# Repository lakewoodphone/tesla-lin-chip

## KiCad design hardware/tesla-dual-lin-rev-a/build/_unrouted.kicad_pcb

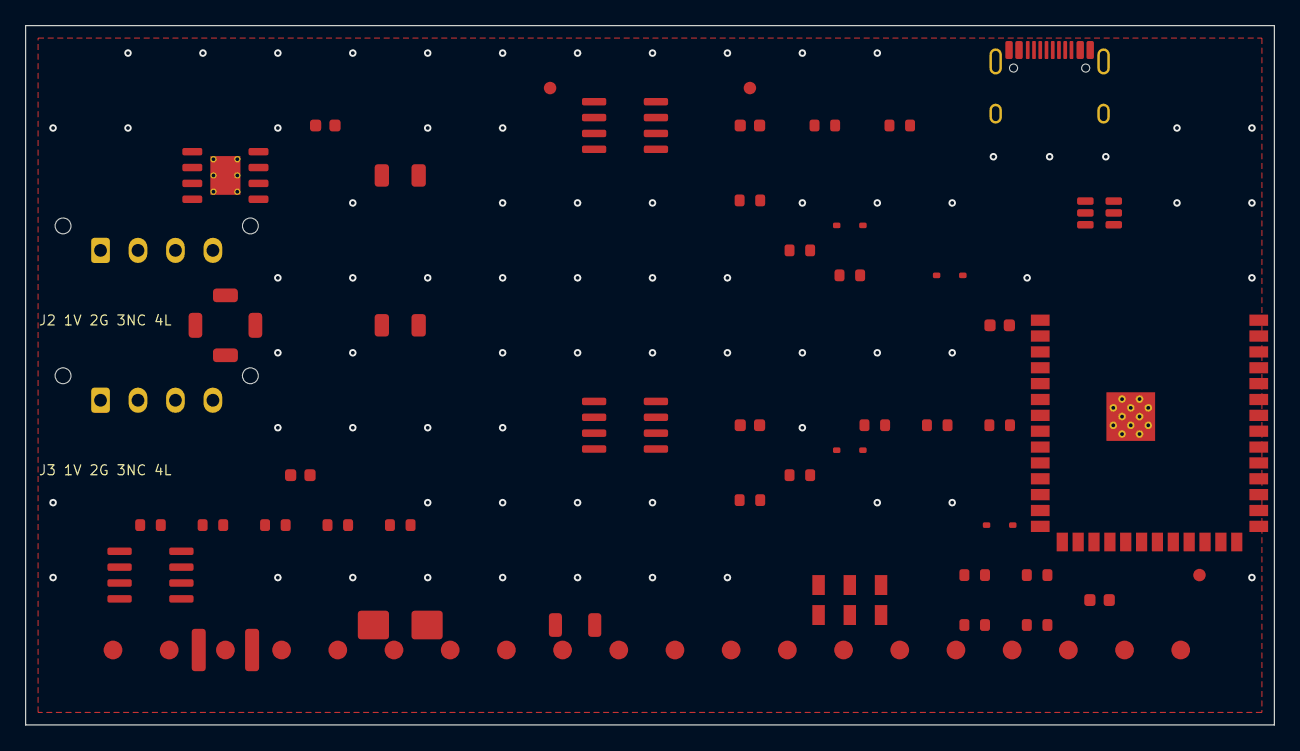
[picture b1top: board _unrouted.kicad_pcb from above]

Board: 4 copper layers, 100.0 x 56.0 mm, 72 parts (0 on the bottom side), 37 nets, no tracks yet.

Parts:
C_3V3: 22uF 10V; C_1206_3216Metric
C_BST1: 100nF; C_0603_1608Metric
C_EN1: 1uF 10V; C_0603_1608Metric
C_IN1: 10uF 50V; C_1206_3216Metric
C_U1_DEC1, C_U2_DEC1, C_U3_DEC1, C_U4_DEC1: 100nF; C_0603_1608Metric
D1: SMBJ24A; D_SMB
D2: LIN_A ESD; D_SOD-323
D3: LIN_B ESD; D_SOD-323
D4: USB ESD; SOT-23-6
D_LINA_MASTER1: DNP LIN master diode; D_SOD-323
D_LINB_MASTER1: DNP LIN master diode; D_SOD-323
F1: 1812 PPTC; Fuse_1812_4532Metric
FB1: 1206 ferrite; L_1206_3216Metric
FID1, FID2, FID3: FID; Fiducial_1mm_Mask2mm
J1: USB-C; USB_C_Receptacle_HRO_TYPE-C-31-M-12
J2: Molex Micro-Fit car service; Molex_Micro-Fit_3.0_43650-0415_1x04_P3.00mm_Vertical
J3: Molex Micro-Fit wheel service; Molex_Micro-Fit_3.0_43650-0415_1x04_P3.00mm_Vertical
L1: 10uH; L_Bourns_SRU5016_5.2x5.2mm
MH1, MH2, MH3, MH4: MH3.2; MountingHole_3.2mm_M3
Q1: AO4407A PFET; SOIC-8_3.9x4.9mm_P1.27mm
R_ARMSENSE_PD1: 0603; R_0603_1608Metric
R_BOOT1: 0603; R_0603_1608Metric
R_BUCK_EN1: 0603; R_0603_1608Metric
R_BUCK_RON1: 0603; R_0603_1608Metric
R_CC1, R_CC2: 0603; R_0603_1608Metric
R_EN1: 0603; R_0603_1608Metric
R_FB_BOT1: 0603; R_0603_1608Metric
R_FB_TOP1: 0603; R_0603_1608Metric
R_LINA_MASTER1: 0603; R_0603_1608Metric
R_LINA_SER1: 0603; R_0603_1608Metric
R_LINA_TXD_PU1: 0603; R_0603_1608Metric
R_LINB_MASTER1: 0603; R_0603_1608Metric
R_LINB_SER1: 0603; R_0603_1608Metric
R_LINB_TXD_PU1: 0603; R_0603_1608Metric
R_LINEN_PD1: 0603; R_0603_1608Metric
R_PGOOD_PU1: 0603; R_0603_1608Metric
R_WAKE_A1: 0603; R_0603_1608Metric
R_WAKE_B1: 0603; R_0603_1608Metric
SW1: DPDT ARM; SW_DPDT_CK_JS202011JCQN
TP1: GND; TestPoint_Pad_D1.5mm
TP2: 3V3; TestPoint_Pad_D1.5mm
TP3: VBAT; TestPoint_Pad_D1.5mm
TP4: USB-; TestPoint_Pad_D1.5mm
TP5: USB+; TestPoint_Pad_D1.5mm
TP6: UART_TX; TestPoint_Pad_D1.5mm
TP7: UART_RX; TestPoint_Pad_D1.5mm
TP8: EN; TestPoint_Pad_D1.5mm
TP9: BOOT; TestPoint_Pad_D1.5mm
TP10: LIN_A; TestPoint_Pad_D1.5mm
TP11: LIN_B; TestPoint_Pad_D1.5mm
TP12: LIN_A_TJA; TestPoint_Pad_D1.5mm
TP13: LIN_B_TJA; TestPoint_Pad_D1.5mm
TP14: LIN_EN; TestPoint_Pad_D1.5mm
TP15: LIN_EN_DRV; TestPoint_Pad_D1.5mm
TP16: ARM; TestPoint_Pad_D1.5mm
TP17: WAKE_A; TestPoint_Pad_D1.5mm
TP18: WAKE_B; TestPoint_Pad_D1.5mm
TP19: INH_A; TestPoint_Pad_D1.5mm
TP20: INH_B; TestPoint_Pad_D1.5mm
U1: ESP32-S3-WROOM-1U
U2: TJA1021T car; SOIC-8_3.9x4.9mm_P1.27mm
U3: TJA1021T wheel; SOIC-8_3.9x4.9mm_P1.27mm
U4: LM5164DDA; HSOP-8-1EP_3.9x4.9mm_P1.27mm_EP2.41x3.1mm_ThermalVias

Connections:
3V3: C_3V3.1, C_U1_DEC1.1, L1.2, R_BOOT1.2, R_EN1.2, R_FB_TOP1.1, R_LINA_TXD_PU1.2, R_LINB_TXD_PU1.2, R_PGOOD_PU1.2, SW1.6, TP2.1, U1.2
ARM_SENSE: R_ARMSENSE_PD1.1, SW1.4, TP16.1, U1.17
BOOT_GPIO0: R_BOOT1.1, TP9.1, U1.27
BUCK_BST: C_BST1.1, U4.7
BUCK_EN: R_BUCK_EN1.2, U4.3
BUCK_FB: R_FB_BOT1.1, R_FB_TOP1.2, U4.5
BUCK_PGOOD: R_PGOOD_PU1.1, U4.6
BUCK_RON: R_BUCK_RON1.2, U4.4
BUCK_SW: C_BST1.2, L1.1, U4.8
CC1: J1.A5, R_CC1.1
CC2: J1.B5, R_CC2.1
EN: C_EN1.1, R_EN1.1, TP8.1, U1.3
GND: C_3V3.2, C_EN1.2, C_IN1.2, C_U1_DEC1.2, C_U2_DEC1.2, C_U3_DEC1.2, C_U4_DEC1.2, D1.2, D2.2, D3.2, D4.2, J1.A1, J1.A12, J1.B1, J1.B12, J1.SH, J2.2, J3.2, Q1.4, R_ARMSENSE_PD1.2, R_CC1.2, R_CC2.2, R_FB_BOT1.2, R_LINEN_PD1.2, SW1.2, SW1.5, TP1.1, U1.1, U1.40, U1.41, U2.5, U3.5, U4.1, U4.9
INH_A_TP: TP19.1, U2.8
INH_B_TP: TP20.1, U3.8
LIN_A: D2.1, J2.4, R_LINA_MASTER1.2, R_LINA_SER1.1, TP10.1
LIN_A_MASTER_PU: D_LINA_MASTER1.2, R_LINA_MASTER1.1
LIN_A_RXD: U1.4, U2.1
LIN_A_TJA: R_LINA_SER1.2, TP12.1, U2.6
LIN_A_TXD: R_LINA_TXD_PU1.1, U1.5, U2.4
LIN_B: D3.1, J3.4, R_LINB_MASTER1.2, R_LINB_SER1.1, TP11.1
LIN_B_MASTER_PU: D_LINB_MASTER1.2, R_LINB_MASTER1.1
LIN_B_RXD: U1.6, U3.1
LIN_B_TJA: R_LINB_SER1.2, TP13.1, U3.6
LIN_B_TXD: R_LINB_TXD_PU1.1, U1.7, U3.4
LIN_EN: R_LINEN_PD1.1, SW1.1, TP14.1, U2.2, U3.2
LIN_EN_DRIVE: SW1.3, TP15.1, U1.12
UART0_RX: TP7.1, U1.36
UART0_TX: TP6.1, U1.37
USB_D_MINUS: D4.1, D4.6, J1.A7, J1.B7, TP4.1, U1.13
USB_D_PLUS: D4.3, D4.4, J1.A6, J1.B6, TP5.1, U1.14
USB_VBUS: D4.5, J1.A4, J1.A9, J1.B4, J1.B9
VBAT_FILTERED: C_IN1.1, C_U4_DEC1.1, FB1.2, R_BUCK_EN1.1, R_BUCK_RON1.1, U4.2
VBAT_IN: F1.1, J2.1, Q1.1, Q1.2, Q1.3
VBAT_PROTECTED: C_U2_DEC1.1, C_U3_DEC1.1, D1.1, D_LINA_MASTER1.1, D_LINB_MASTER1.1, F1.2, FB1.1, J3.1, Q1.5, Q1.6, Q1.7, Q1.8, R_WAKE_A1.2, R_WAKE_B1.2, TP3.1, U2.7, U3.7
WAKE_A_N: R_WAKE_A1.1, TP17.1, U2.3
WAKE_B_N: R_WAKE_B1.1, TP18.1, U3.3
